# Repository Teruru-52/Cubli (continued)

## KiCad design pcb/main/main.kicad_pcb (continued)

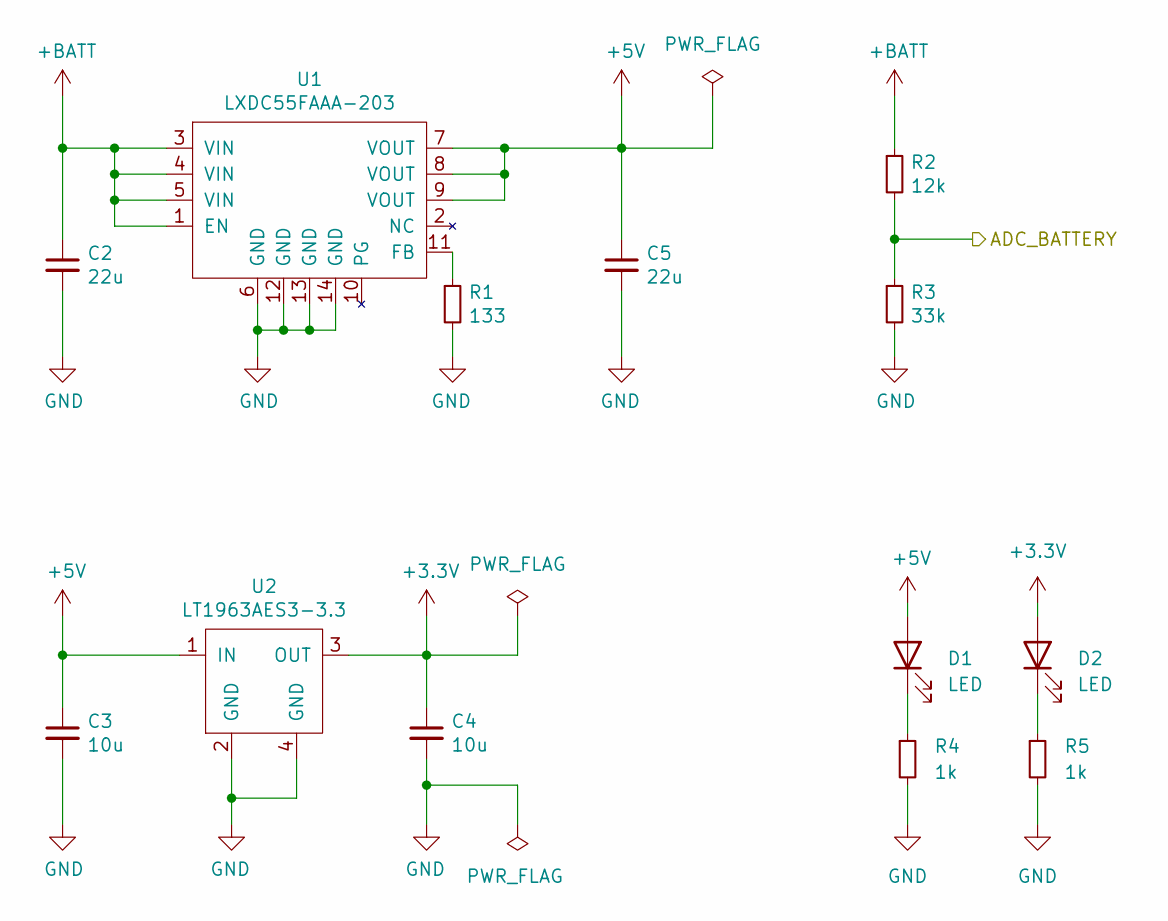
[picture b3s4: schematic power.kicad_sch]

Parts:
C2, C5: 22u; C_0805_2012Metric_Pad1.18x1.45mm_HandSolder
C3, C4: 10u; C_0805_2012Metric_Pad1.18x1.45mm_HandSolder
D1, D2: LED; LED_0603_1608Metric
R1: 133; R_0805_2012Metric
R2: 12k; R_0603_1608Metric
R3: 33k; R_0603_1608Metric
R4, R5: 1k; R_0603_1608Metric_Pad0.98x0.95mm_HandSolder
U1: LXDC55FAAA-203
U2: LT1963AES3-3.3; SOT-223

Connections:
+3.3V: C4.1, D2.2 (A), U2.3 (OUT); also elsewhere on the board
+5V: C3.1, C5.1, D1.2 (A), U1.7 (VOUT), U1.8 (VOUT), U1.9 (VOUT), U2.1 (IN); also elsewhere on the board
+BATT: C2.1, R2.1, U1.1 (EN), U1.3 (VIN), U1.4 (VIN), U1.5 (VIN); also elsewhere on the board
/power/ADC_BATTERY: R2.2, R3.1; also elsewhere on the board
GND: C2.2, C3.2, C4.2, C5.2, R1.2, R3.2, R4.2, R5.2, U1.6 (GND), U1.12 (GND), U1.13 (GND), U1.14 (GND), U2.2 (GND), U2.4 (GND); also elsewhere on the board
unnamed: D1.1 (K), R4.1
unnamed: D2.1 (K), R5.1
unnamed: R1.1, U1.11 (FB)

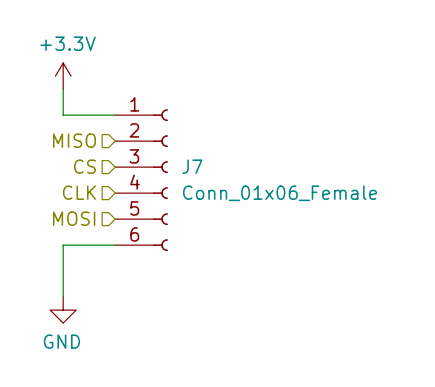
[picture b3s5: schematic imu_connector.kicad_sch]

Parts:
J7: Conn_01x06_Female; JST_ZE_SM06B-ZESS-TB_1x06-1MP_P1.50mm_Horizontal

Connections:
+3.3V: J7.1; also elsewhere on the board
/imu/SPI_CLK: J7.4; also elsewhere on the board
/imu/SPI_MISO: J7.2; also elsewhere on the board
/imu/SPI_MOSI: J7.5; also elsewhere on the board
/stm32f405rg/SPI2_CS6: J7.3; also elsewhere on the board
GND: J7.6; also elsewhere on the board

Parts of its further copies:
J2, J3, J4, J5, J6: Conn_01x06_Female; JST_ZE_SM06B-ZESS-TB_1x06-1MP_P1.50mm_Horizontal

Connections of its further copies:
+3.3V: J2.1, J3.1, J4.1, J5.1, J6.1; also elsewhere on the board
/imu/SPI_CLK: J2.4, J3.4, J4.4, J5.4, J6.4; also elsewhere on the board
/imu/SPI_MISO: J2.2, J3.2, J4.2, J5.2, J6.2; also elsewhere on the board
/imu/SPI_MOSI: J2.5, J3.5, J4.5, J5.5, J6.5; also elsewhere on the board
/stm32f405rg/SPI2_CS1: J2.3; also elsewhere on the board
/stm32f405rg/SPI2_CS2: J3.3; also elsewhere on the board
/stm32f405rg/SPI2_CS3: J4.3; also elsewhere on the board
/stm32f405rg/SPI2_CS4: J5.3; also elsewhere on the board
/stm32f405rg/SPI2_CS5: J6.3; also elsewhere on the board
GND: J2.6, J3.6, J4.6, J5.6, J6.6; also elsewhere on the board

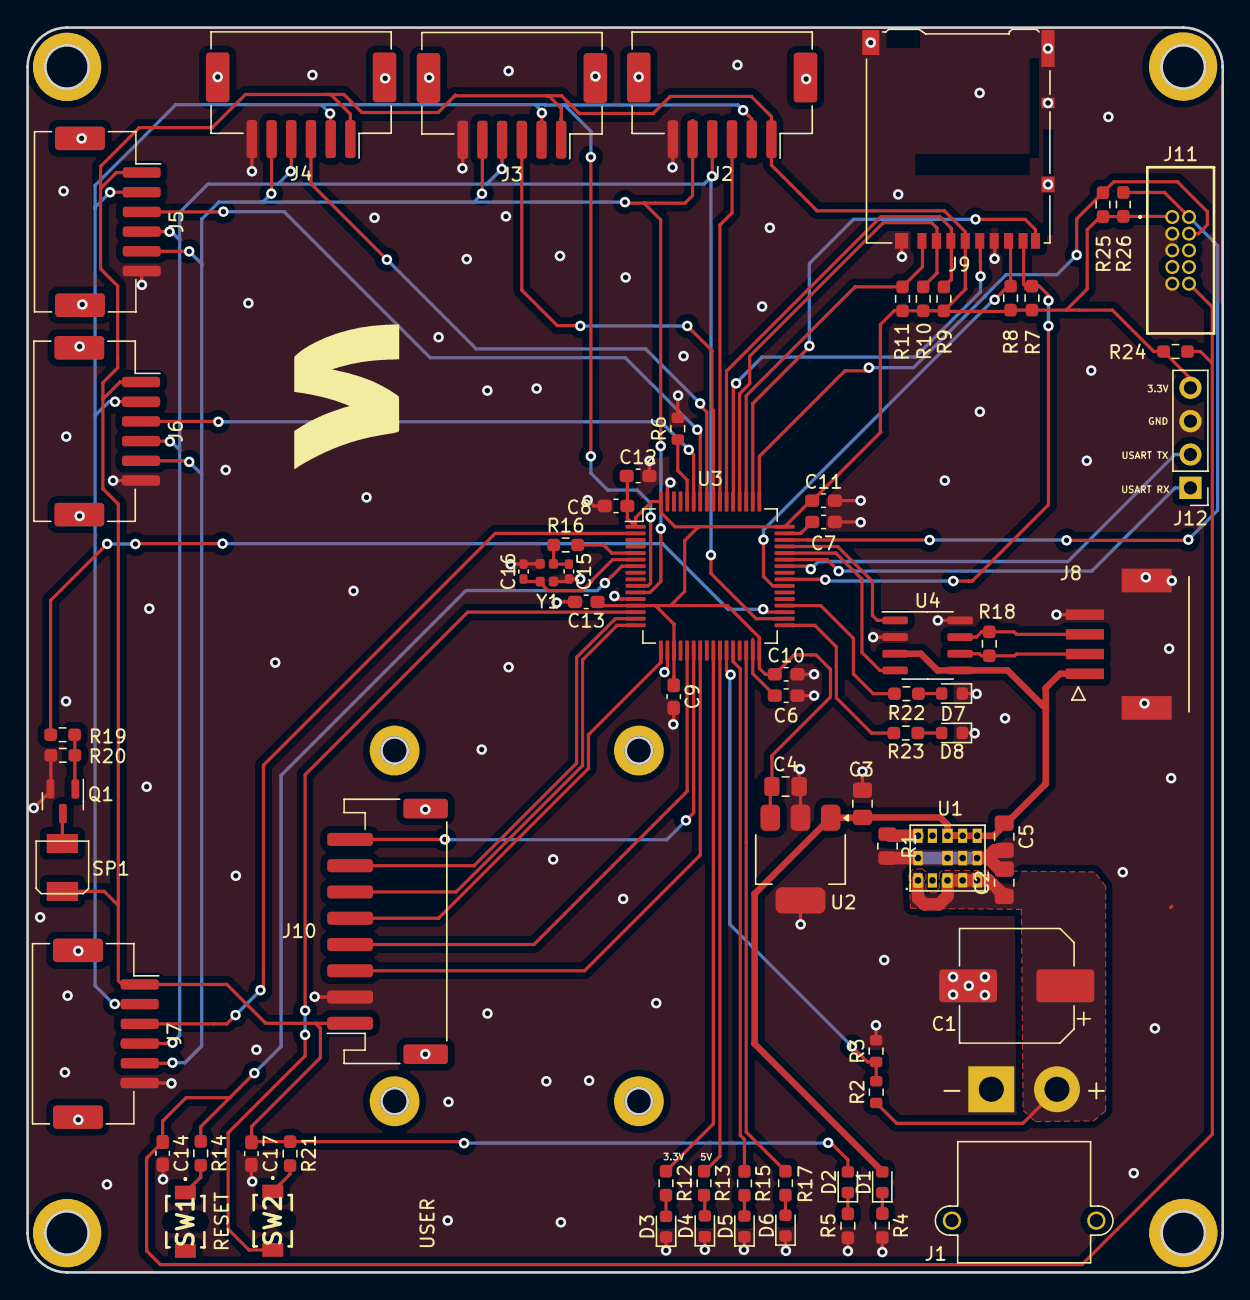
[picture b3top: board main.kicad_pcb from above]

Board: 2 copper layers, 91.0 x 94.8 mm, 80 parts (0 on the bottom side), 62 nets.

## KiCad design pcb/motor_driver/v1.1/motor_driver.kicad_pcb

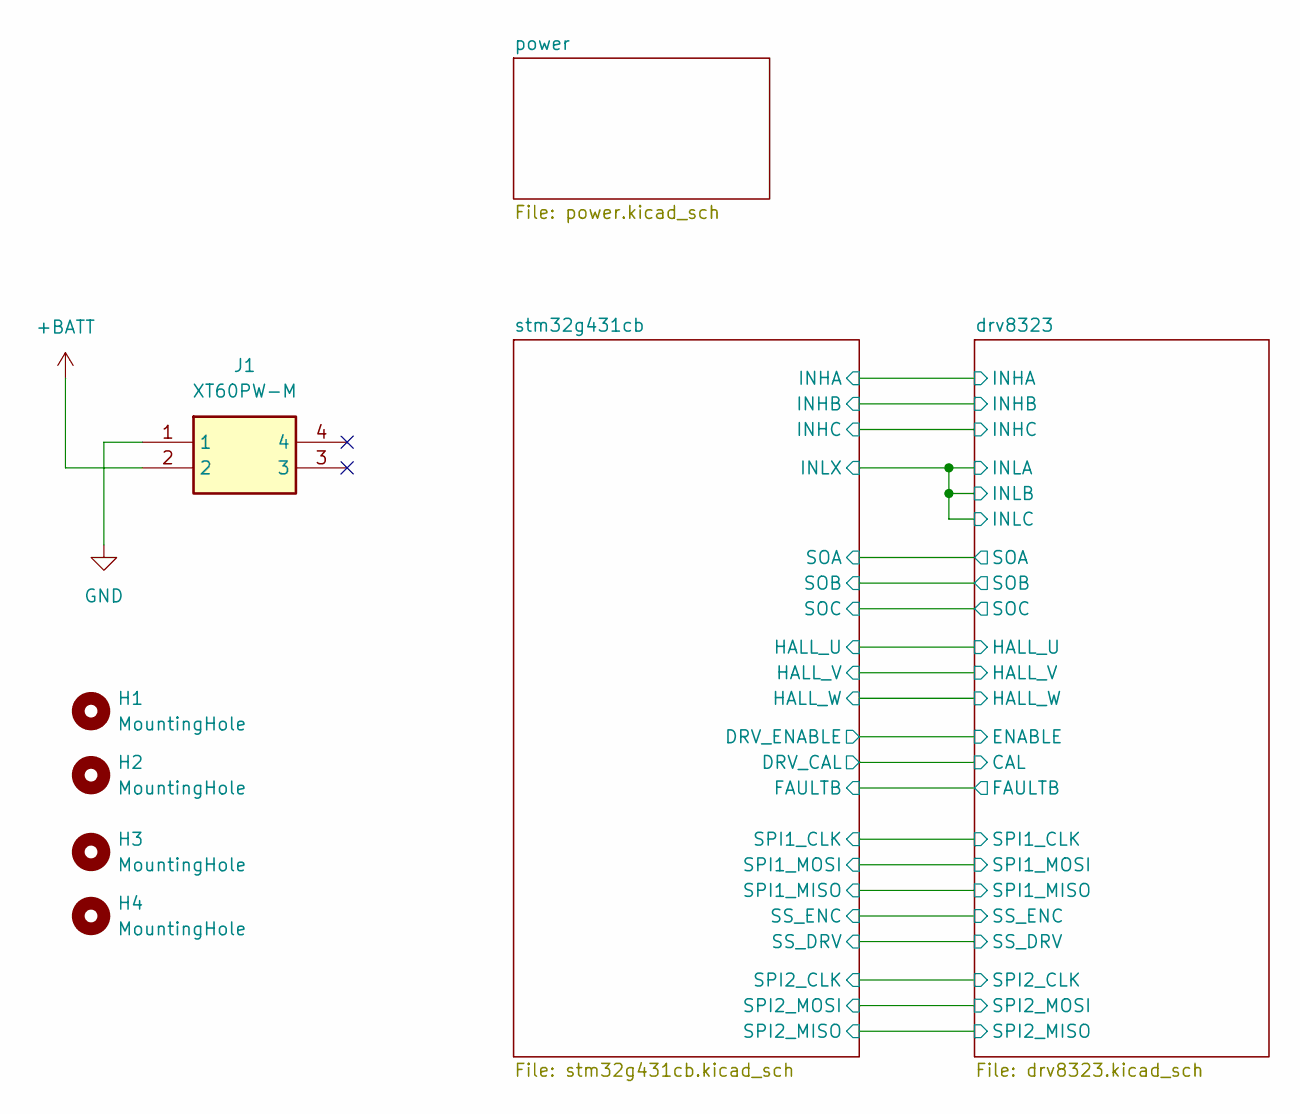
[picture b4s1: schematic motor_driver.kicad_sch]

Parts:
H1, H2, H3, H4: MountingHole; MountingHole_3.2mm_M3_Pad_TopBottom
J1: XT60PW-M; AMASS_XT60-M_1x02_P7.20mm_Vertical; Manufacturer_Part_Number XT60PW-M

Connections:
+BATT: J1.2; also elsewhere on the board

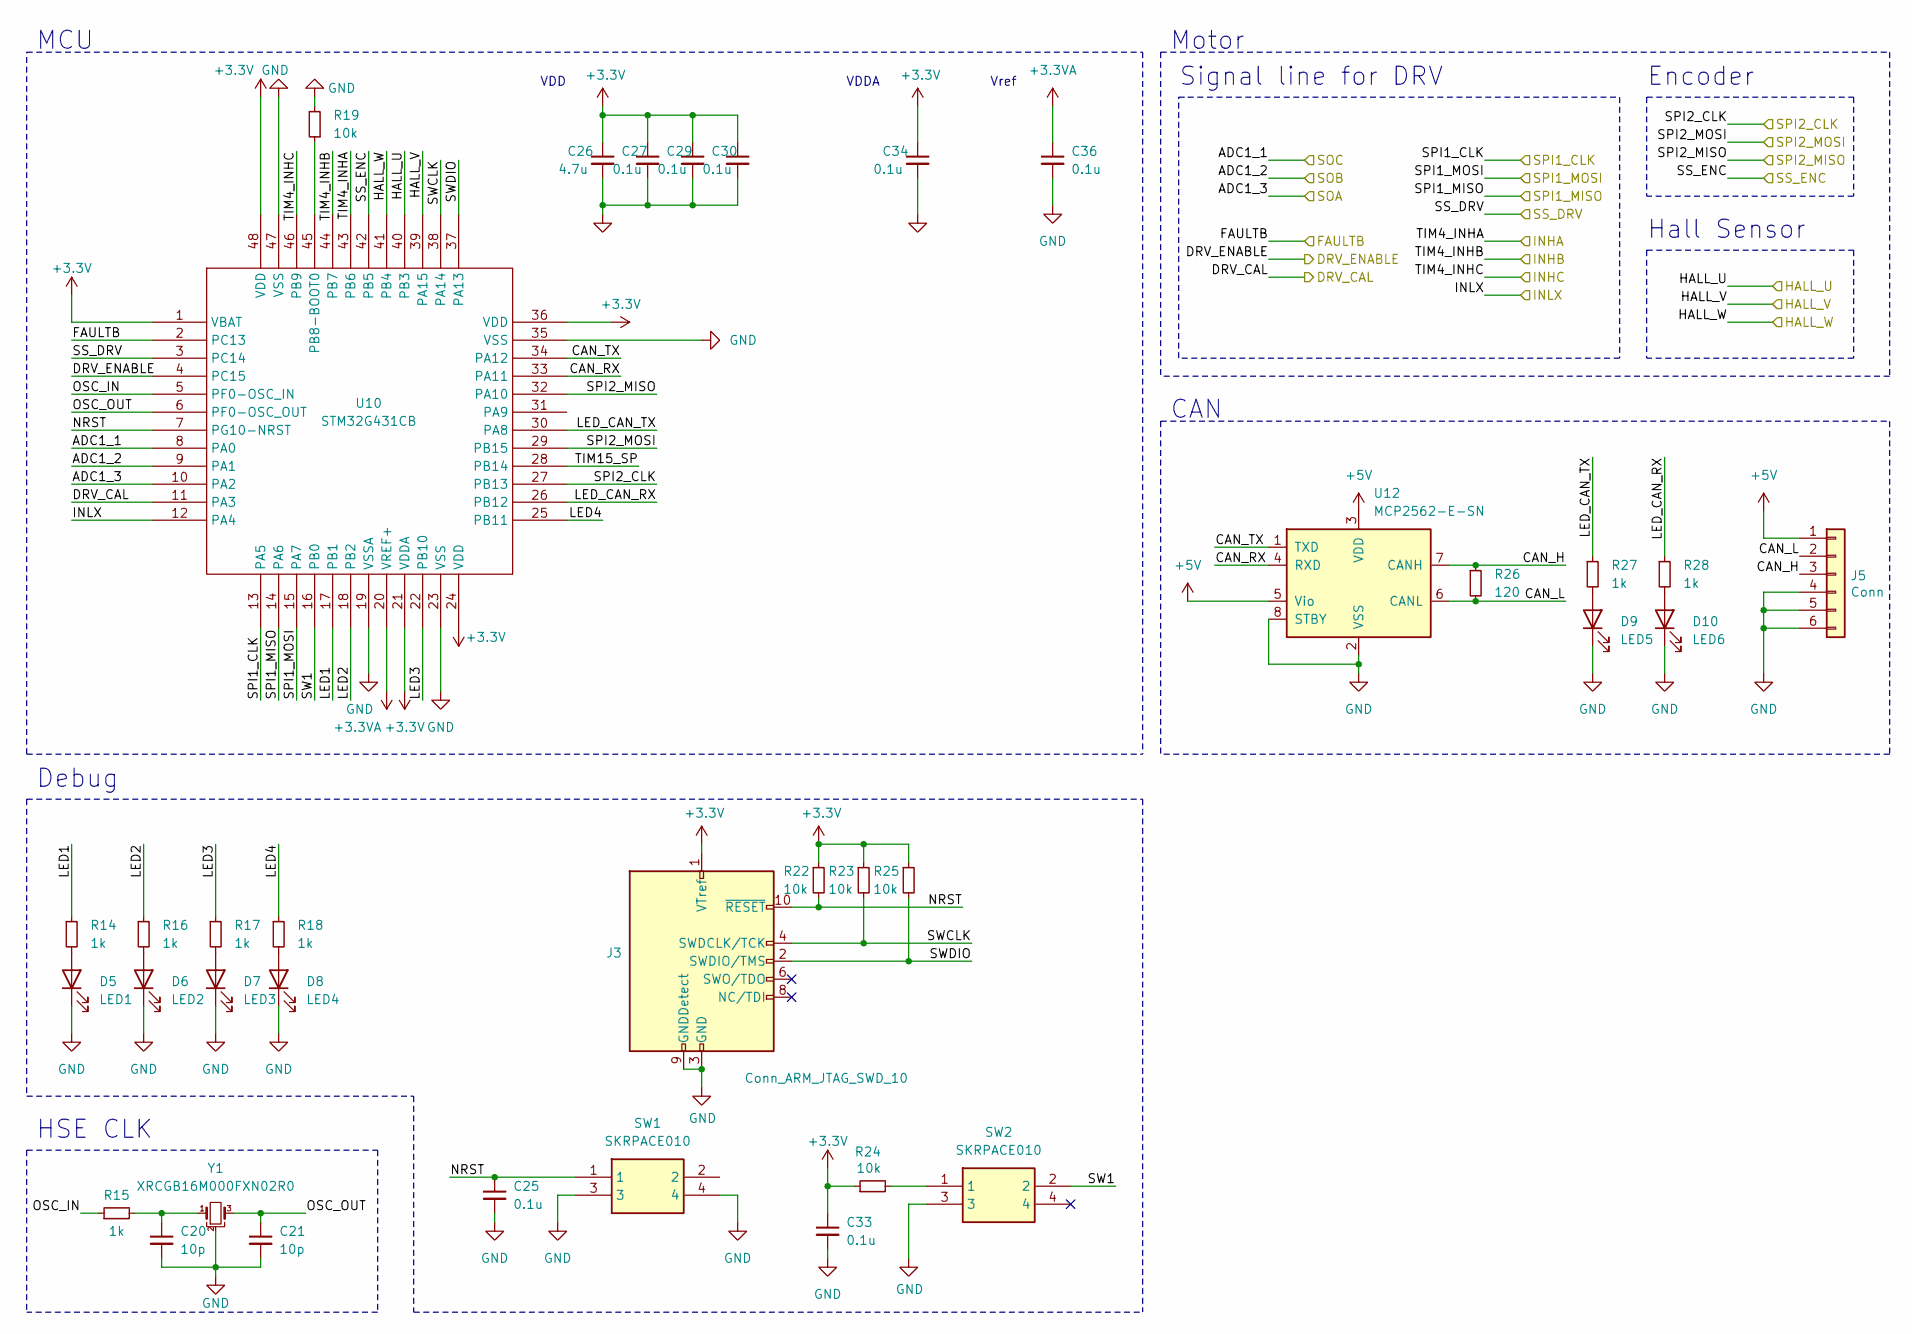
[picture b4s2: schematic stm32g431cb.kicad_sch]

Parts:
C20, C21: 10p; C_0402_1005Metric_Pad0.74x0.62mm_HandSolder
C25, C33: 0.1u; C_0603_1608Metric_Pad1.08x0.95mm_HandSolder
C26: 4.7u; C_0402_1005Metric
C27, C29, C30, C36: 0.1u; C_0201_0603Metric
C34: 0.1u; C_0402_1005Metric
D5: LED1; LED_0402_1005Metric
D6: LED2; LED_0402_1005Metric
D7: LED3; LED_0402_1005Metric
D8: LED4; LED_0402_1005Metric
D9: LED5; LED_0402_1005Metric
D10: LED6; LED_0402_1005Metric
J3: Conn_ARM_JTAG_SWD_10; PinHeader_2x05_P1.27mm_Vertical
J5: Conn; 21322604YY
R14, R16, R17, R18, R27, R28: 1k; R_0603_1608Metric_Pad0.98x0.95mm_HandSolder
R15: 1k; R_0402_1005Metric_Pad0.72x0.64mm_HandSolder
R19: 10k; R_0603_1608Metric_Pad0.98x0.95mm_HandSolder
R22, R23, R24, R25: 10k; R_0201_0603Metric
R26: 120; R_0603_1608Metric_Pad0.98x0.95mm_HandSolder
SW1, SW2: SKRPACE010; Manufacturer_Part_Number SKRPACE010; Mouser Part Number 688-SKRPACE010
U10: STM32G431CB; LQFP-48_7x7mm_P0.5mm
U12: MCP2562-E-SN; SOIC-8_3.9x4.9mm_P1.27mm
Y1: XRCGB16M000FXN02R0

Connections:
+3.3V: C26.1, C27.1, C29.1, C30.1, C33.1, C34.1, J3.1 (VTref), R22.1, R23.1, R24.1, R25.1, U10.1 (VBAT), U10.21 (VDDA), U10.24 (VDD), U10.36 (VDD), U10.48 (VDD); also elsewhere on the board
+3.3VA: C36.1, U10.20 (VREF+); also elsewhere on the board
+5V: J5.1, U12.3 (VDD), U12.5 (Vio); also elsewhere on the board
/drv8323/HALL_U: U10.40 (PB3); also elsewhere on the board
/drv8323/HALL_V: U10.39 (PA15); also elsewhere on the board
/drv8323/HALL_W: U10.41 (PB4); also elsewhere on the board
/drv8323/INHA: U10.43 (PB6); also elsewhere on the board
/drv8323/INHB: U10.44 (PB7); also elsewhere on the board
/drv8323/INHC: U10.46 (PB9); also elsewhere on the board
/drv8323/SPI1_CLK: U10.13 (PA5); also elsewhere on the board
/drv8323/SPI1_MISO: U10.14 (PA6); also elsewhere on the board
/drv8323/SPI1_MOSI: U10.15 (PA7); also elsewhere on the board
/drv8323/SPI2_CLK: U10.27 (PB13); also elsewhere on the board
/drv8323/SPI2_MISO: U10.32 (PA10); also elsewhere on the board
/drv8323/SPI2_MOSI: U10.29 (PB15); also elsewhere on the board
/drv8323/SS_ENC: U10.42 (PB5); also elsewhere on the board
/stm32g431cb/ADC1_1: U10.8 (PA0); also elsewhere on the board
/stm32g431cb/ADC1_2: U10.9 (PA1); also elsewhere on the board
/stm32g431cb/ADC1_3: U10.10 (PA2); also elsewhere on the board
/stm32g431cb/CAN_H: J5.3, R26.1, U12.7 (CANH)
/stm32g431cb/CAN_L: J5.2, R26.2, U12.6 (CANL)
/stm32g431cb/CAN_RX: U10.33 (PA11), U12.4 (RXD)
/stm32g431cb/CAN_TX: U10.34 (PA12), U12.1 (TXD)
/stm32g431cb/DRV_CAL: U10.11 (PA3); also elsewhere on the board
/stm32g431cb/DRV_ENABLE: U10.4 (PC15); also elsewhere on the board
/stm32g431cb/FAULTB: U10.2 (PC13); also elsewhere on the board
/stm32g431cb/INLX: U10.12 (PA4); also elsewhere on the board
/stm32g431cb/LED1: R14.1, U10.17 (PB1)
/stm32g431cb/LED2: R16.1, U10.18 (PB2)
/stm32g431cb/LED3: R17.1, U10.22 (PB10)
/stm32g431cb/LED4: R18.1, U10.25 (PB11)
/stm32g431cb/LED_CAN_RX: R28.1, U10.26 (PB12)
/stm32g431cb/LED_CAN_TX: R27.1, U10.30 (PA8)
/stm32g431cb/OSC_IN: R15.1, U10.5 (PF0-OSC_IN)
/stm32g431cb/OSC_OUT: C21.1, U10.6 (PF0-OSC_OUT), Y1.3
/stm32g431cb/SS_DRV: U10.3 (PC14); also elsewhere on the board
/stm32g431cb/SW1: SW2.2, U10.16 (PB0)
/stm32g431cb/SWCLK: J3.4 (SWDCLK/TCK), R23.2, U10.38 (PA14)
/stm32g431cb/SWDIO: J3.2 (SWDIO/TMS), R25.2, U10.37 (PA13)
/stm32g431cb/TIM15_SP: U10.28 (PB14); also elsewhere on the board
unnamed: C20.1, R15.2, Y1.1
unnamed: D5.2 (A), R14.2
unnamed: D6.2 (A), R16.2
unnamed: D7.2 (A), R17.2
unnamed: D8.2 (A), R18.2
unnamed: D9.2 (A), R27.2
unnamed: D10.2 (A), R28.2
unnamed: R19.1, U10.45 (PB8-BOOT0)
unnamed: R24.2, SW2.1

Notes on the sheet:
Motor
HSE CLK
MCU
CAN
Encoder
Signal line for DRV
Debug
VDD
Vref
VDDA
Hall Sensor

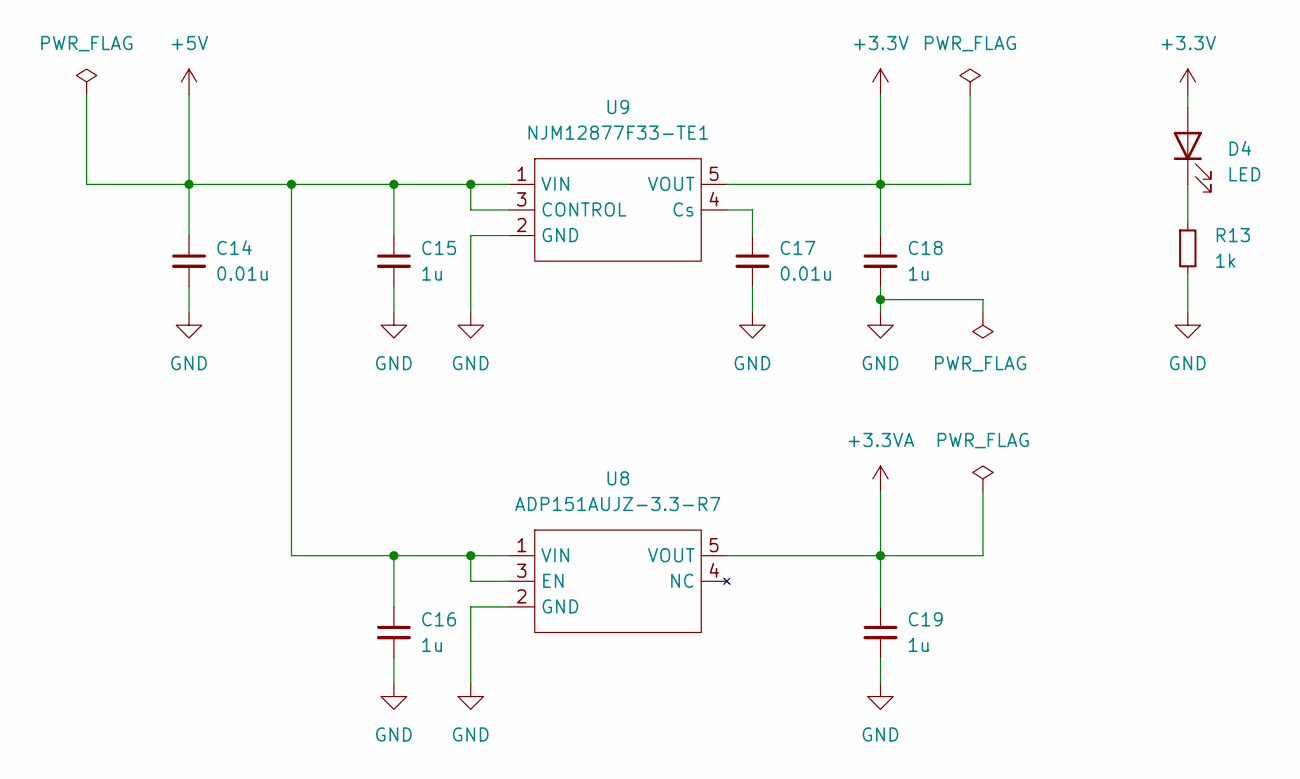
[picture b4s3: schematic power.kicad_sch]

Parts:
C14, C17: 0.01u; C_0603_1608Metric_Pad1.08x0.95mm_HandSolder
C15, C16, C18, C19: 1u; C_0603_1608Metric_Pad1.08x0.95mm_HandSolder
D4: LED; LED_0603_1608Metric_Pad1.05x0.95mm_HandSolder
R13: 1k; R_0402_1005Metric_Pad0.72x0.64mm_HandSolder
U8: ADP151AUJZ-3.3-R7; SOT-23-5_HandSoldering
U9: NJM12877F33-TE1; SOT-23-5_HandSoldering

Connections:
+3.3V: C18.1, D4.2 (A), U9.5 (VOUT); also elsewhere on the board
+3.3VA: C19.1, U8.5 (VOUT); also elsewhere on the board
+5V: C14.1, C15.1, C16.1, U8.1 (VIN), U8.3 (EN), U9.1 (VIN), U9.3 (CONTROL); also elsewhere on the board
unnamed: C17.1, U9.4 (Cs)
unnamed: D4.1 (K), R13.1

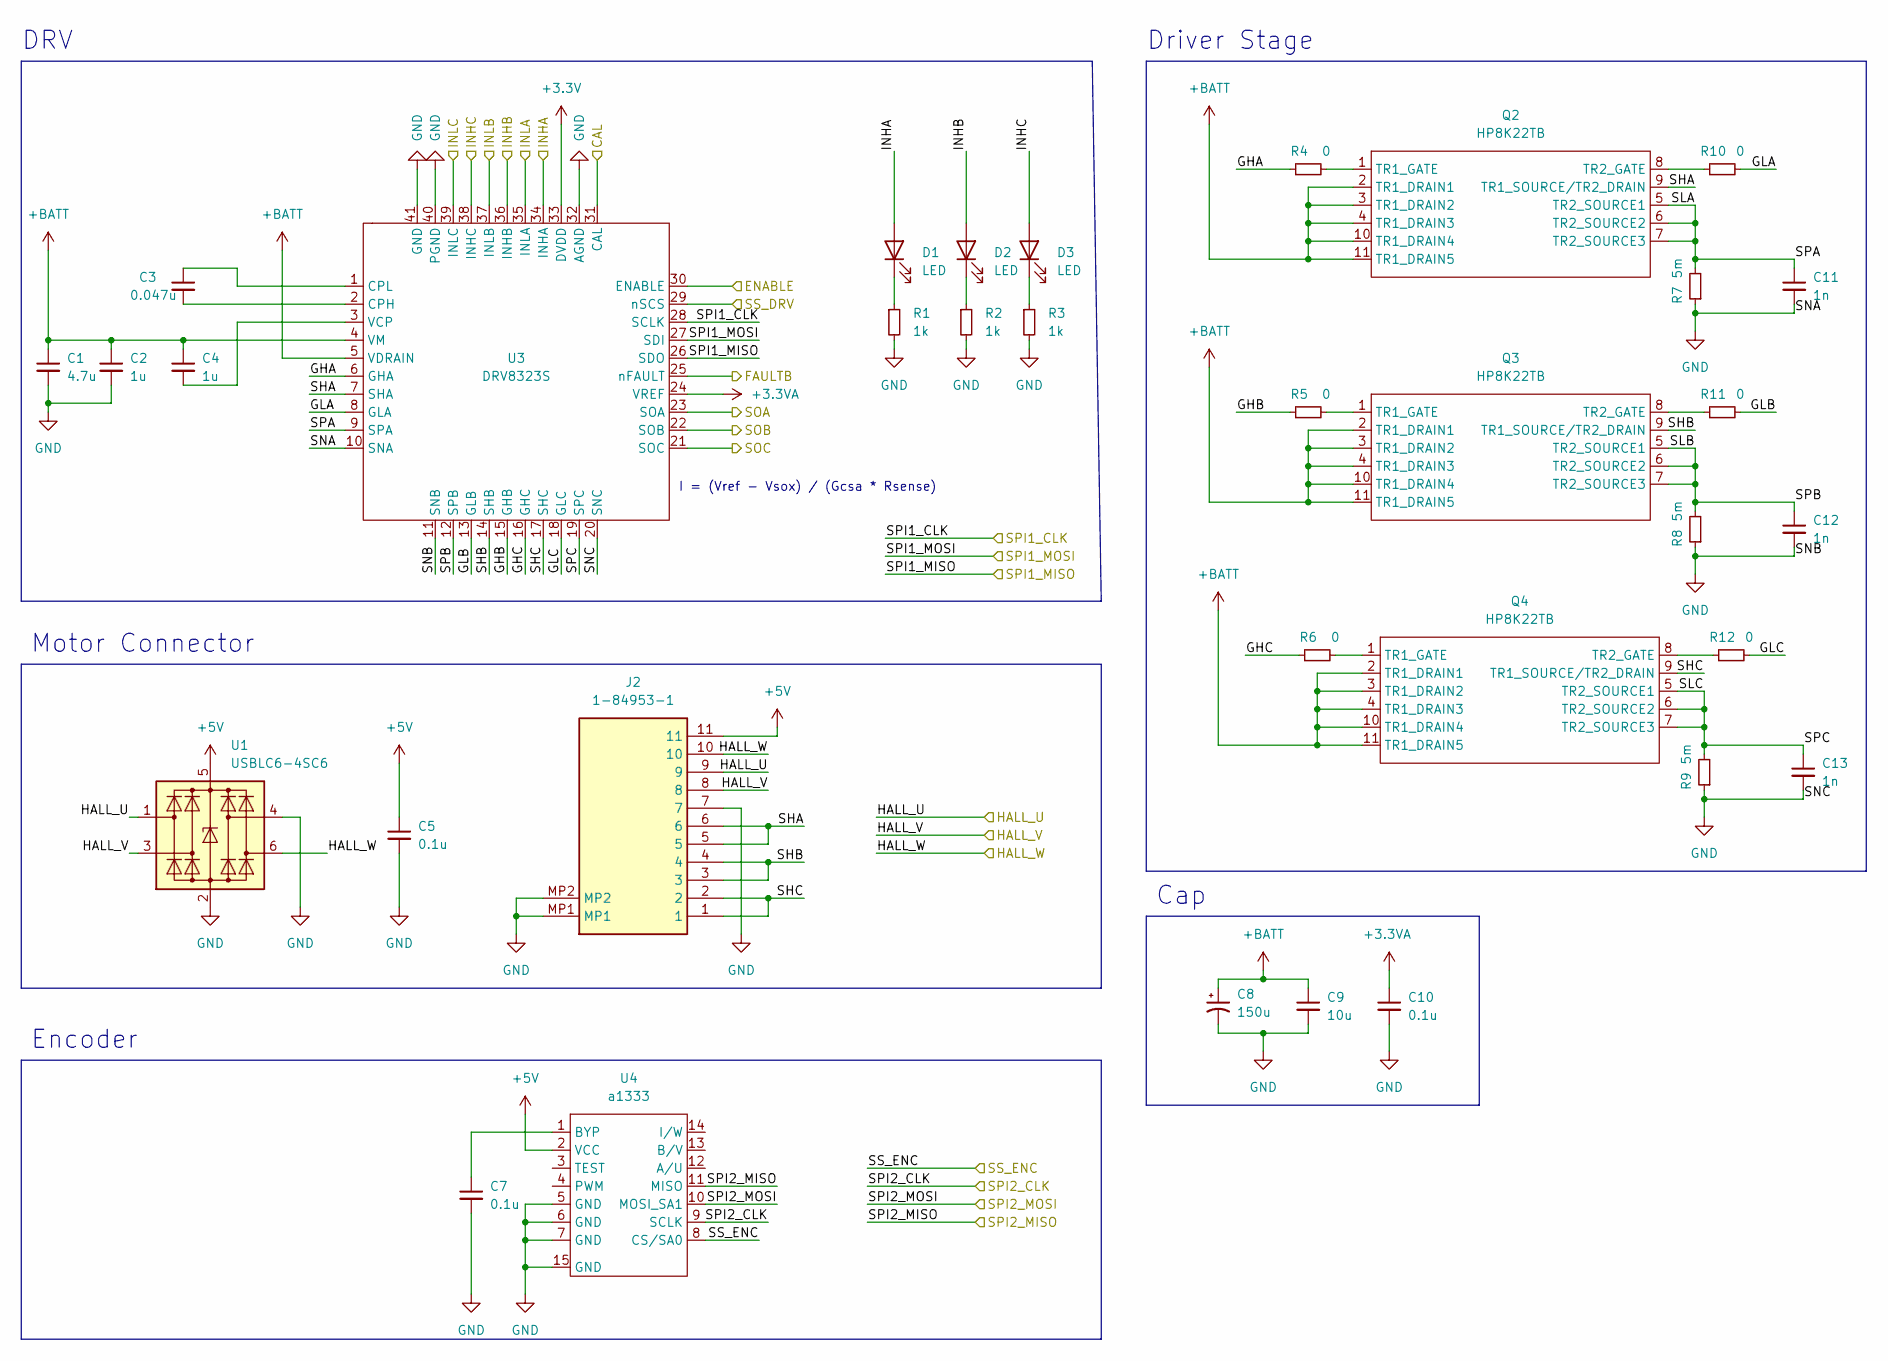
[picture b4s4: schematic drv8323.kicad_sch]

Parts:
C1: 4.7u; C_0603_1608Metric_Pad1.08x0.95mm_HandSolder
C2, C4: 1u; C_0603_1608Metric_Pad1.08x0.95mm_HandSolder
C3: 0.047u; C_0603_1608Metric_Pad1.08x0.95mm_HandSolder
C5, C7: 0.1u; C_0603_1608Metric_Pad1.08x0.95mm_HandSolder
C8: 150u; CP_Elec_8x10.5
C9: 10u; C_0603_1608Metric_Pad1.08x0.95mm_HandSolder
C10: 0.1u; C_0402_1005Metric_Pad0.74x0.62mm_HandSolder
C11, C12, C13: 1n; C_0402_1005Metric_Pad0.74x0.62mm_HandSolder
D1, D2, D3: LED; LED_0603_1608Metric_Pad1.05x0.95mm_HandSolder
J2: 1-84953-1; Manufacturer_Part_Number 1-84953-1; Mouser Part Number 571-1-84953-1
Q2, Q3, Q4: HP8K22TB; HP8K24TB
R1, R2, R3: 1k; R_0402_1005Metric_Pad0.72x0.64mm_HandSolder
R4, R5, R6, R10, R11, R12: 0; R_0805_2012Metric_Pad1.20x1.40mm_HandSolder
R7, R8, R9: 5m; R_2010_5025Metric_Pad1.40x2.65mm_HandSolder
U1: USBLC6-4SC6; SOT-23-6
U3: DRV8323S; QFN-40-1EP_6x6mm_P0.5mm_EP4.6x4.6mm_ThermalVias
U4: a1333; HTSSOP-14-1EP_4.4x5mm_P0.65mm_EP3.4x5mm_Mask3x3.1mm

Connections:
+3.3V: U3.33 (DVDD); also elsewhere on the board
+3.3VA: C10.1, U3.24 (VREF); also elsewhere on the board
+5V: C5.1, J2.11, U1.5 (VBUS), U4.2 (VCC); also elsewhere on the board
+BATT: C1.1, C2.1, C4.1, C8.1, C9.1, Q2.2 (TR1_DRAIN1), Q2.3 (TR1_DRAIN2), Q2.4 (TR1_DRAIN3), Q2.10 (TR1_DRAIN4), Q2.11 (TR1_DRAIN5), Q3.2 (TR1_DRAIN1), Q3.3 (TR1_DRAIN2), Q3.4 (TR1_DRAIN3), Q3.10 (TR1_DRAIN4), Q3.11 (TR1_DRAIN5), Q4.2 (TR1_DRAIN1), Q4.3 (TR1_DRAIN2), Q4.4 (TR1_DRAIN3), Q4.10 (TR1_DRAIN4), Q4.11 (TR1_DRAIN5), U3.4 (VM), U3.5 (VDRAIN); also elsewhere on the board
/drv8323/GHA: R4.1, U3.6 (GHA)
/drv8323/GHB: R5.1, U3.15 (GHB)
/drv8323/GHC: R6.1, U3.16 (GHC)
/drv8323/GLA: R10.2, U3.8 (GLA)
/drv8323/GLB: R11.2, U3.13 (GLB)
/drv8323/GLC: R12.2, U3.18 (GLC)
/drv8323/HALL_U: J2.9, U1.1 (I/O1); also elsewhere on the board
/drv8323/HALL_V: J2.8, U1.3 (I/O2); also elsewhere on the board
/drv8323/HALL_W: J2.10, U1.6 (I/O4); also elsewhere on the board
/drv8323/INHA: D1.2 (A), U3.34 (INHA); also elsewhere on the board
/drv8323/INHB: D2.2 (A), U3.36 (INHB); also elsewhere on the board
/drv8323/INHC: D3.2 (A), U3.38 (INHC); also elsewhere on the board
/drv8323/SHA: J2.5, J2.6, Q2.9 (TR1_SOURCE/TR2_DRAIN), U3.7 (SHA)
/drv8323/SHB: J2.3, J2.4, Q3.9 (TR1_SOURCE/TR2_DRAIN), U3.14 (SHB)
/drv8323/SHC: J2.1, J2.2, Q4.9 (TR1_SOURCE/TR2_DRAIN), U3.17 (SHC)
/drv8323/SLA: C11.1, Q2.5 (TR2_SOURCE1), Q2.6 (TR2_SOURCE2), Q2.7 (TR2_SOURCE3), R7.2, U3.9 (SPA)
/drv8323/SLB: C12.1, Q3.5 (TR2_SOURCE1), Q3.6 (TR2_SOURCE2), Q3.7 (TR2_SOURCE3), R8.2, U3.12 (SPB)
/drv8323/SLC: C13.1, Q4.5 (TR2_SOURCE1), Q4.6 (TR2_SOURCE2), Q4.7 (TR2_SOURCE3), R9.2, U3.19 (SPC)
/drv8323/SPI1_CLK: U3.28 (SCLK); also elsewhere on the board
/drv8323/SPI1_MISO: U3.26 (SDO); also elsewhere on the board
/drv8323/SPI1_MOSI: U3.27 (SDI); also elsewhere on the board
/drv8323/SPI2_CLK: U4.9 (SCLK); also elsewhere on the board
/drv8323/SPI2_MISO: U4.11 (MISO); also elsewhere on the board
/drv8323/SPI2_MOSI: U4.10 (MOSI_SA1); also elsewhere on the board
/drv8323/SS_ENC: U4.8 (CS/SA0); also elsewhere on the board
/stm32g431cb/ADC1_1: U3.21 (SOC); also elsewhere on the board
/stm32g431cb/ADC1_2: U3.22 (SOB); also elsewhere on the board
/stm32g431cb/ADC1_3: U3.23 (SOA); also elsewhere on the board
/stm32g431cb/DRV_CAL: U3.31 (CAL); also elsewhere on the board
/stm32g431cb/DRV_ENABLE: U3.30 (ENABLE); also elsewhere on the board
/stm32g431cb/FAULTB: U3.25 (nFAULT); also elsewhere on the board
/stm32g431cb/INLX: U3.35 (INLA), U3.37 (INLB), U3.39 (INLC); also elsewhere on the board
/stm32g431cb/SS_DRV: U3.29 (nSCS); also elsewhere on the board
unnamed: C3.1, U3.1 (CPL)
unnamed: C3.2, U3.2 (CPH)
unnamed: C4.2, U3.3 (VCP)
unnamed: C7.1, U4.1 (BYP)
unnamed: D1.1 (K), R1.1
unnamed: D2.1 (K), R2.1
unnamed: D3.1 (K), R3.1
unnamed: Q2.1 (TR1_GATE), R4.2
unnamed: Q2.8 (TR2_GATE), R10.1
unnamed: Q3.1 (TR1_GATE), R5.2
unnamed: Q3.8 (TR2_GATE), R11.1
unnamed: Q4.1 (TR1_GATE), R6.2
unnamed: Q4.8 (TR2_GATE), R12.1

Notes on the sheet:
Driver Stage
DRV
Motor Connector
Cap
Encoder
I = (Vref - Vsox) / (Gcsa * Rsense)

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
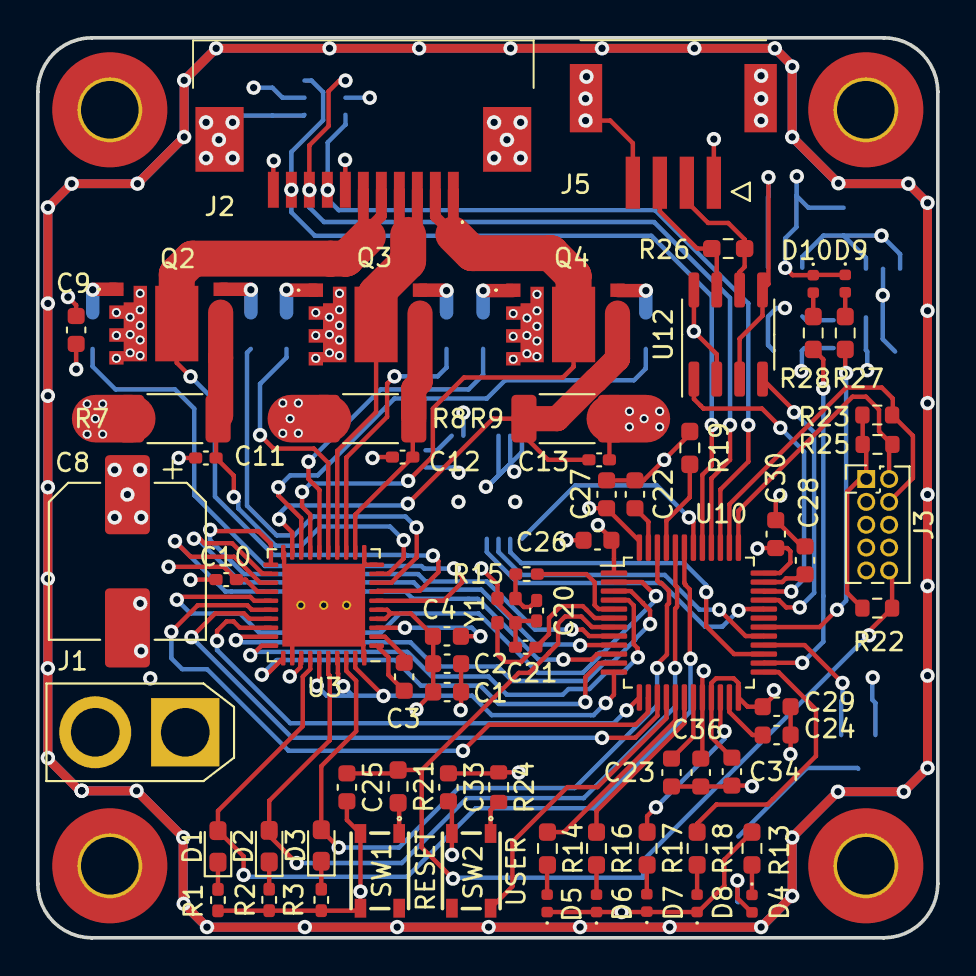
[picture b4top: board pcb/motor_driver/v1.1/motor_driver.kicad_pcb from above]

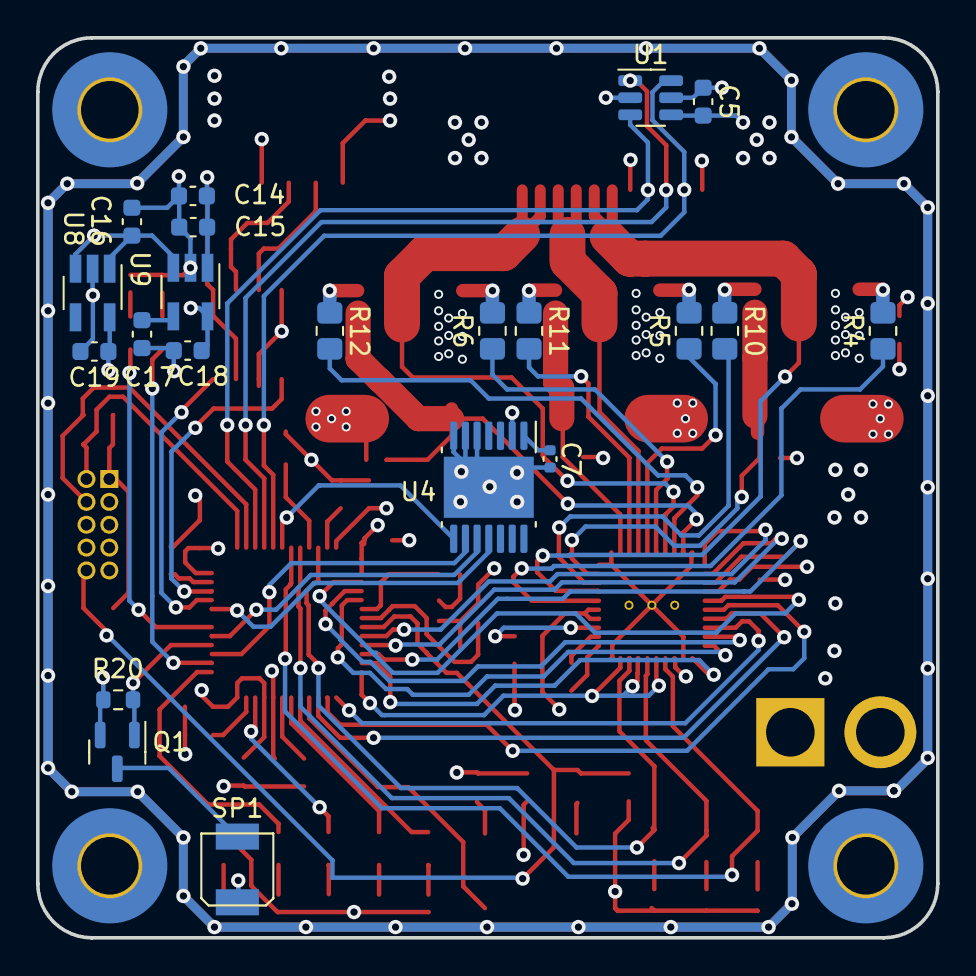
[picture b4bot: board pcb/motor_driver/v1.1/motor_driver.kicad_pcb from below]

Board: 4 copper layers, 50.0 x 50.0 mm, 93 parts (21 on the bottom side), 85 nets.

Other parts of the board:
C22, C23, C24, C28: 2.2u; C_0603_1608Metric
Q1: BSS138; SOT-23
R20: 100k; R_0603_1608Metric
R21: 1k; R_0603_1608Metric_Pad0.98x0.95mm_HandSolder
SP1: SMT-0440; STM0440-T-R

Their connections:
+3.3V: SP1.1; also elsewhere on the board
/stm32g431cb/TIM15_SP: Q1.1 (G), R20.1; also elsewhere on the board
unnamed: Q1.3 (D), SP1.2

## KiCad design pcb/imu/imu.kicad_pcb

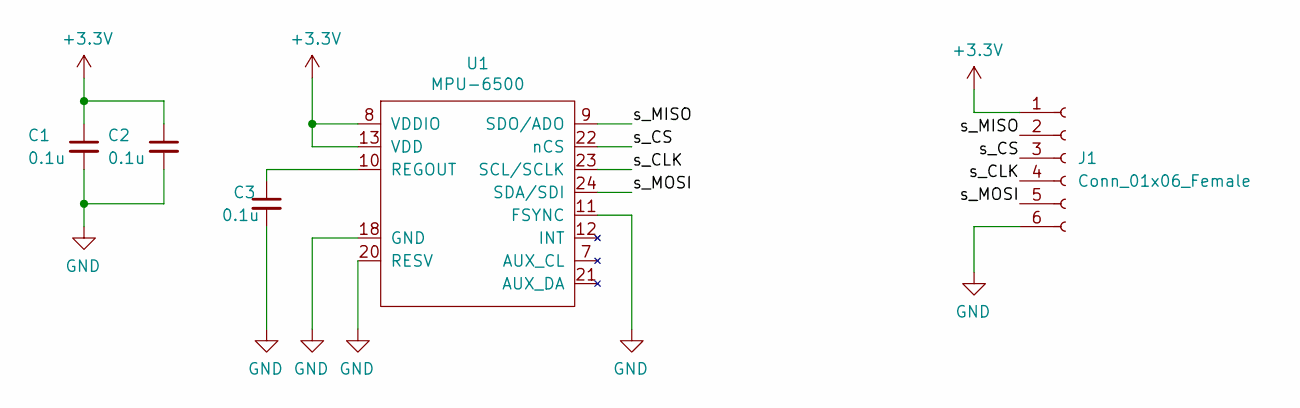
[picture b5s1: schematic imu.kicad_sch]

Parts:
C1, C2, C3: 0.1u; C_0603_1608Metric_Pad1.08x0.95mm_HandSolder
J1: Conn_01x06_Female; JST_ZE_BM06B-ZESS-TBT_1x06-1MP_P1.50mm_Vertical
U1: MPU-6500; QFN-24-1EP_3x3mm_P0.4mm_EP1.75x1.6mm

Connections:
+3.3V: C1.1, C2.1, J1.1, U1.8 (VDDIO), U1.13 (VDD)
/s_CLK: J1.4, U1.23 (SCL/SCLK)
/s_CS: J1.3, U1.22 (nCS)
/s_MISO: J1.2, U1.9 (SDO/ADO)
/s_MOSI: J1.5, U1.24 (SDA/SDI)
GND: C1.2, C2.2, C3.2, J1.6, U1.11 (FSYNC), U1.18 (GND), U1.20 (RESV)
unnamed: C3.1, U1.10 (REGOUT)

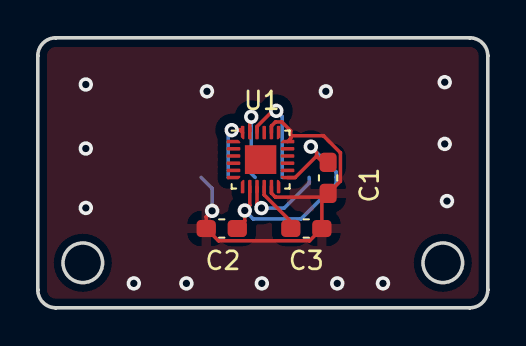
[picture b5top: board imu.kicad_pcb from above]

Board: 2 copper layers, 25.0 x 15.0 mm, 5 parts (1 on the bottom side), 7 nets.

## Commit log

2023-08-14 update pcb
2023-08-14 add blmd dxf
2023-08-14 add basic function
2023-08-15 add .gitignore
2023-08-15 add calculation of angular velocity
2023-08-15 add dxf
2023-10-04 feat: LCD module
2023-10-04 feat: SEGGER jLink
2023-10-04 chore: add circuit git changes
2023-10-04 chore: delete build files
2023-10-04 feat: calculate sensor position
2023-10-04 feat: vscode settings
2023-10-04 feat: FATFS
2023-10-04 feat: matlab simulation
2023-10-04 feat: update source
2023-10-04 feat: add .gitignore
2023-10-08 chore: add pcb backups
2023-10-08 feat: add freertos for mb
2023-10-08 chore: debugging LCD
2023-10-08 chore: FATFS settings
2023-10-08 feat: add functions (CAN, sensors, FreeRTOS)
2023-10-08 fix: imu potision
2023-10-08 feat: add functions (CAN, IMU)
2023-10-08 chore: update .gitignore
2023-10-26 chore: debug
2023-10-26 feat: add freertos
2023-10-26 feat: add GPIO Interruption
2023-10-26 fix: remove GPIO Interruption
2023-11-05 chore: try to fix bug
2024-01-12 feat: fix most bug
2024-04-28 feat: Update firmware
2024-05-18 chore: commit before starting to develop v1.2
2024-05-18 chore: add v1.2
2024-06-11 perf: fix pcb for v1.2
2024-06-11 feat: finish adding a connector
2024-07-26 feat: finish main board v2
2024-07-26 chore' add backup files
2024-08-02 perf: update motor driver pdb
2024-08-02 perf: edit SW footprint
2024-08-03 wip: can settings
2024-08-03 perf: enable to use jlink
2024-08-04 feat: enable to CAN communication!
2024-08-09 perf: update LCD and microSD
2024-08-09 feat: delete two CAN connectors & add microSD input pin
2024-08-09 chore: generate code
2024-08-09 feat: add additional CAN connetctor
2024-08-09 feat: add DC jack & change XT30 footprint
2024-08-09 chore: add backups
2024-08-14 chore: add gerber
2024-09-01 perf: change control frequency
2024-09-01 chore: add pcb buckups
2024-09-03 chore: add pcb backup
2024-09-19 feat: enable to turn on LEDs
2024-09-19 chore(wip): change clock
2024-09-20 chore(wip): check LEDs
2024-09-20 feat: enable CAN communication
2024-09-20 perf(wip): can settings
2024-09-20 perf: can interuppt settings
2024-09-20 perf: can communication speed
2024-09-20 chore: can settings
2024-09-21 feat: update encoder
2024-09-22 feat: dma for current sense
2024-09-22 feat: spi & inject transform
2024-09-23 fix: spi2 (encoder) config
2024-09-23 feat: enabe to use display
2024-09-23 feat(wip): SDIO settings
2024-09-26 refactor: files & directories
2024-09-26 feat: can receive callback & send
2024-09-27 refactor: driver
2024-09-27 fear: add LPF
2024-09-27 refactor: motor driver
2024-09-27 fix: foc bug
2024-09-27 refactor: function name & unnecessary variables
2024-09-28 refactor: hall sensor & driver
2024-09-29 perf: add fault check for driver
2024-09-29 fix: UVW assignment
2024-09-29 fix: process hall senser
2024-10-02 refactor: drv8323 register settings
2024-10-03 perf: process fault messages
2024-10-06 chore: add Kicad backup
2024-10-06 perf: updaet driver controller
